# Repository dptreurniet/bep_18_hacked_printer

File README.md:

# bep_18_hacked_printer
Hacking a desktop inkjet printer to print micro-devices

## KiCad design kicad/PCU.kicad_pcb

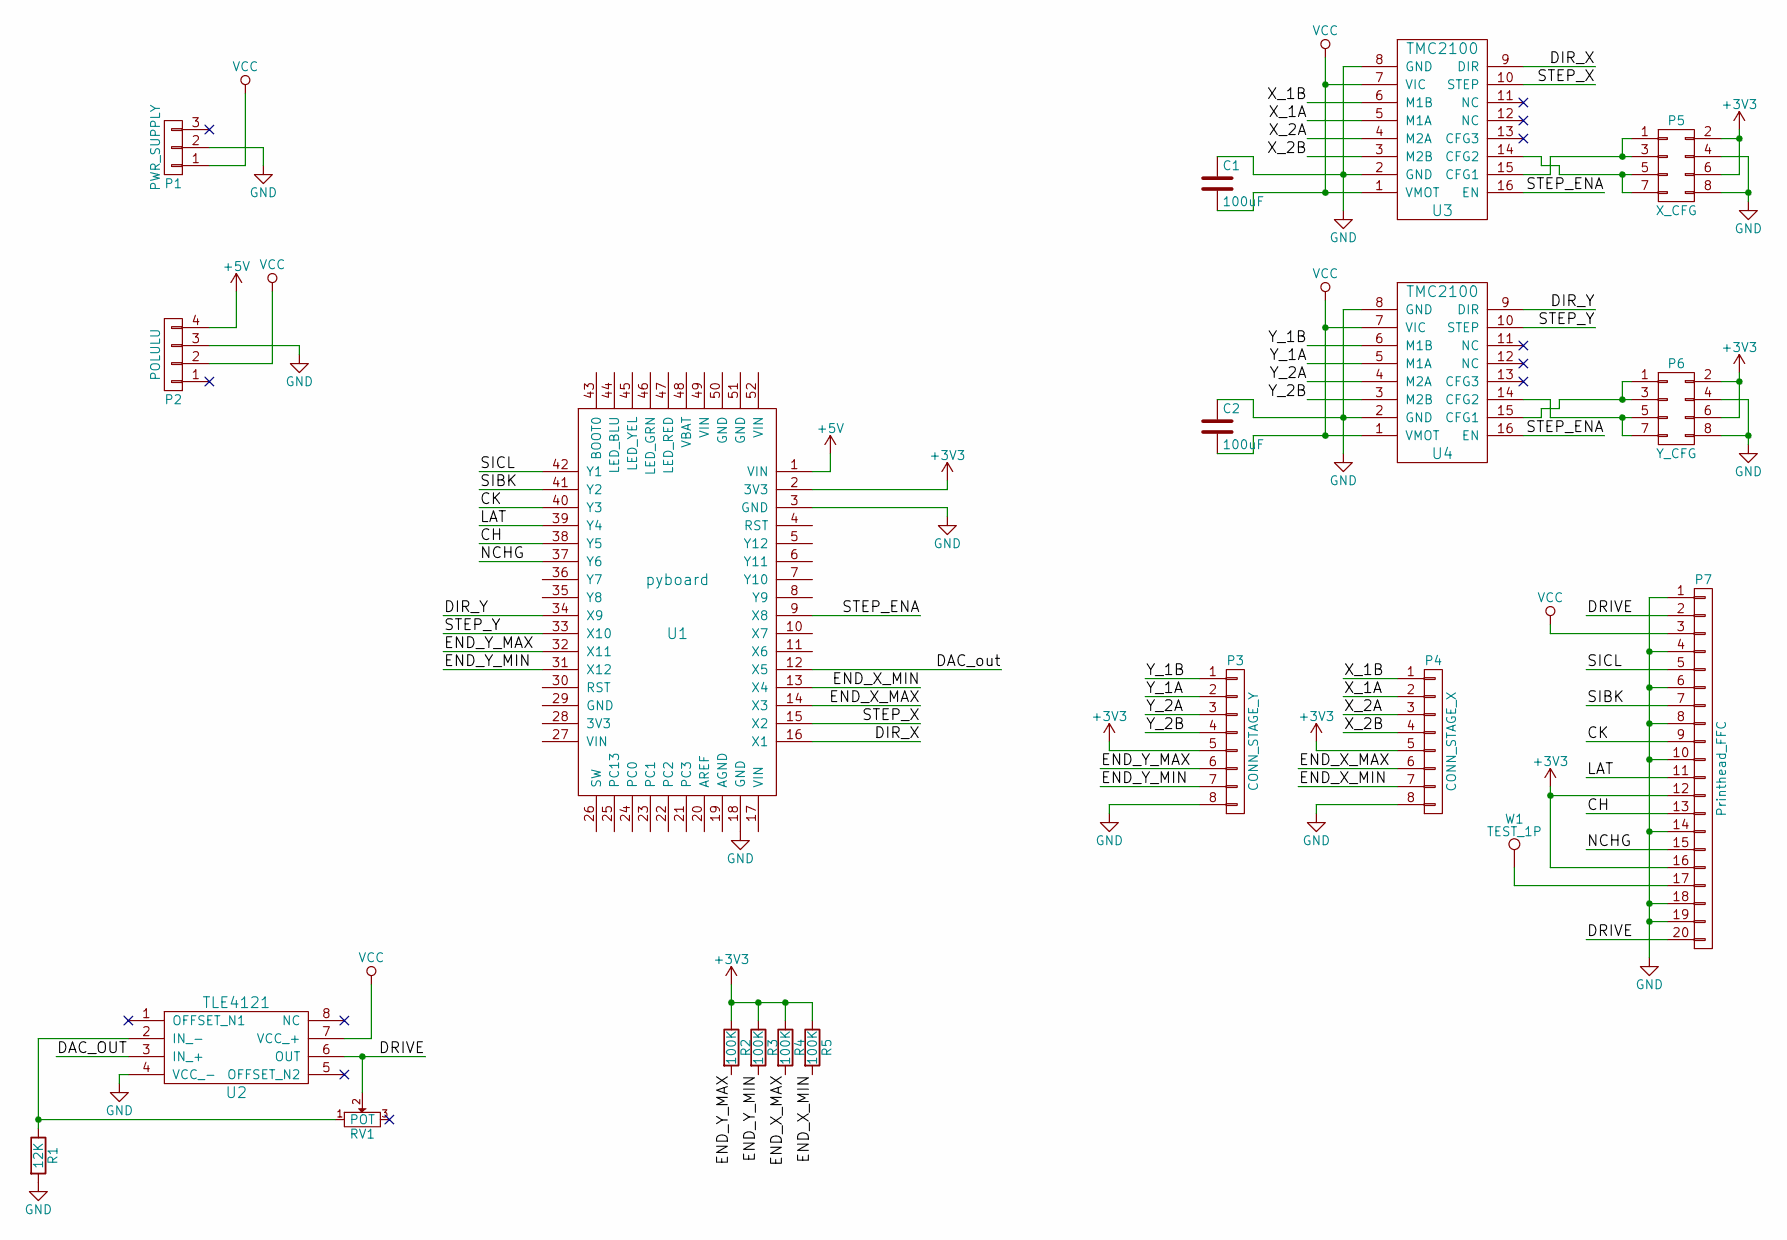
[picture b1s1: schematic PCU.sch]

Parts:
C1, C2: 100uF; Capacitor_D8_L11.5
P1: PWR_SUPPLY; Pin_Header_Straight_1x03
P2: POLULU; Polulu
P3: CONN_STAGE_Y; Pin_Header_Straight_1x08
P4: CONN_STAGE_X; Pin_Header_Straight_1x08
P5: X_CFG; Pin_Header_Straight_2x04
P6: Y_CFG; Pin_Header_Straight_2x04
P7: Printhead_FFC; 52030-2029
R1: 12K; Resistor_Horizontal_RM10mm
R2, R3, R4, R5: 100K; Resistor_Horizontal_RM10mm
RV1: POT; Potentiometer_Bourns_3339W_Angular_ScrewFront
U1: pyboard; Pyboard
U2: TLE4121; DIP-8_W7.62mm
U3, U4: TMC2100
W1: TEST_1P; SolderWirePad_single_1mmDrill

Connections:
+3V3: P3.5, P4.5, P5.2, P5.6, P6.2, P6.6, P7.12, P7.16, R2.1, R3.1, R4.1, R5.1, U1.2 (3V3)
+5V: P2.4, U1.1 (VIN)
/CH: P7.13, U1.38 (Y5)
/CK: P7.9, U1.40 (Y3)
/DAC_OUT: U1.12 (X5), U2.3 (IN_+)
/DIR_X: U1.16 (X1), U3.9 (DIR)
/DIR_Y: U1.34 (X9), U4.9 (DIR)
/DRIVE: P7.2, P7.20, RV1.2, U2.6 (OUT)
/END_X_MAX: P4.6, R4.2, U1.14 (X3)
/END_X_MIN: P4.7, R5.2, U1.13 (X4)
/END_Y_MAX: P3.6, R2.2, U1.32 (X11)
/END_Y_MIN: P3.7, R3.2, U1.31 (X12)
/LAT: P7.11, U1.39 (Y4)
/NCHG: P7.15, U1.37 (Y6)
/SIBK: P7.7, U1.41 (Y2)
/SICL: P7.5, U1.42 (Y1)
/STEP_ENA: U1.9 (X8), U3.16 (EN), U4.16 (EN)
/STEP_X: U1.15 (X2), U3.10 (STEP)
/STEP_Y: U1.33 (X10), U4.10 (STEP)
/X_1A: P4.2, U3.5 (M1A)
/X_1B: P4.1, U3.6 (M1B)
/X_2A: P4.3, U3.4 (M2A)
/X_2B: P4.4, U3.3 (M2B)
/Y_1A: P3.2, U4.5 (M1A)
/Y_1B: P3.1, U4.6 (M1B)
/Y_2A: P3.3, U4.4 (M2A)
/Y_2B: P3.4, U4.3 (M2B)
GND: C1.1, C2.1, P1.2, P2.3, P3.8, P4.8, P5.4, P5.8, P6.4, P6.8, P7.1, P7.4, P7.6, P7.8, P7.10, P7.14, P7.18, P7.19, R1.2, U1.3 (GND), U1.18 (GND), U2.4 (VCC_-), U3.2 (GND), U3.8 (GND), U4.2 (GND), U4.8 (GND)
unnamed: P5.1, P5.3, U3.15 (CFG1)
unnamed: P5.5, P5.7, U3.14 (CFG2)
unnamed: P6.1, P6.3, U4.15 (CFG1)
unnamed: P6.5, P6.7, U4.14 (CFG2)
unnamed: P7.17, W1.1
unnamed: R1.1, RV1.1, U2.2 (IN_-)
VCC: C1.2, C2.2, P1.1, P2.2, P7.3, U2.7 (VCC_+), U3.1 (VMOT), U3.7 (VIC), U4.1 (VMOT), U4.7 (VIC)

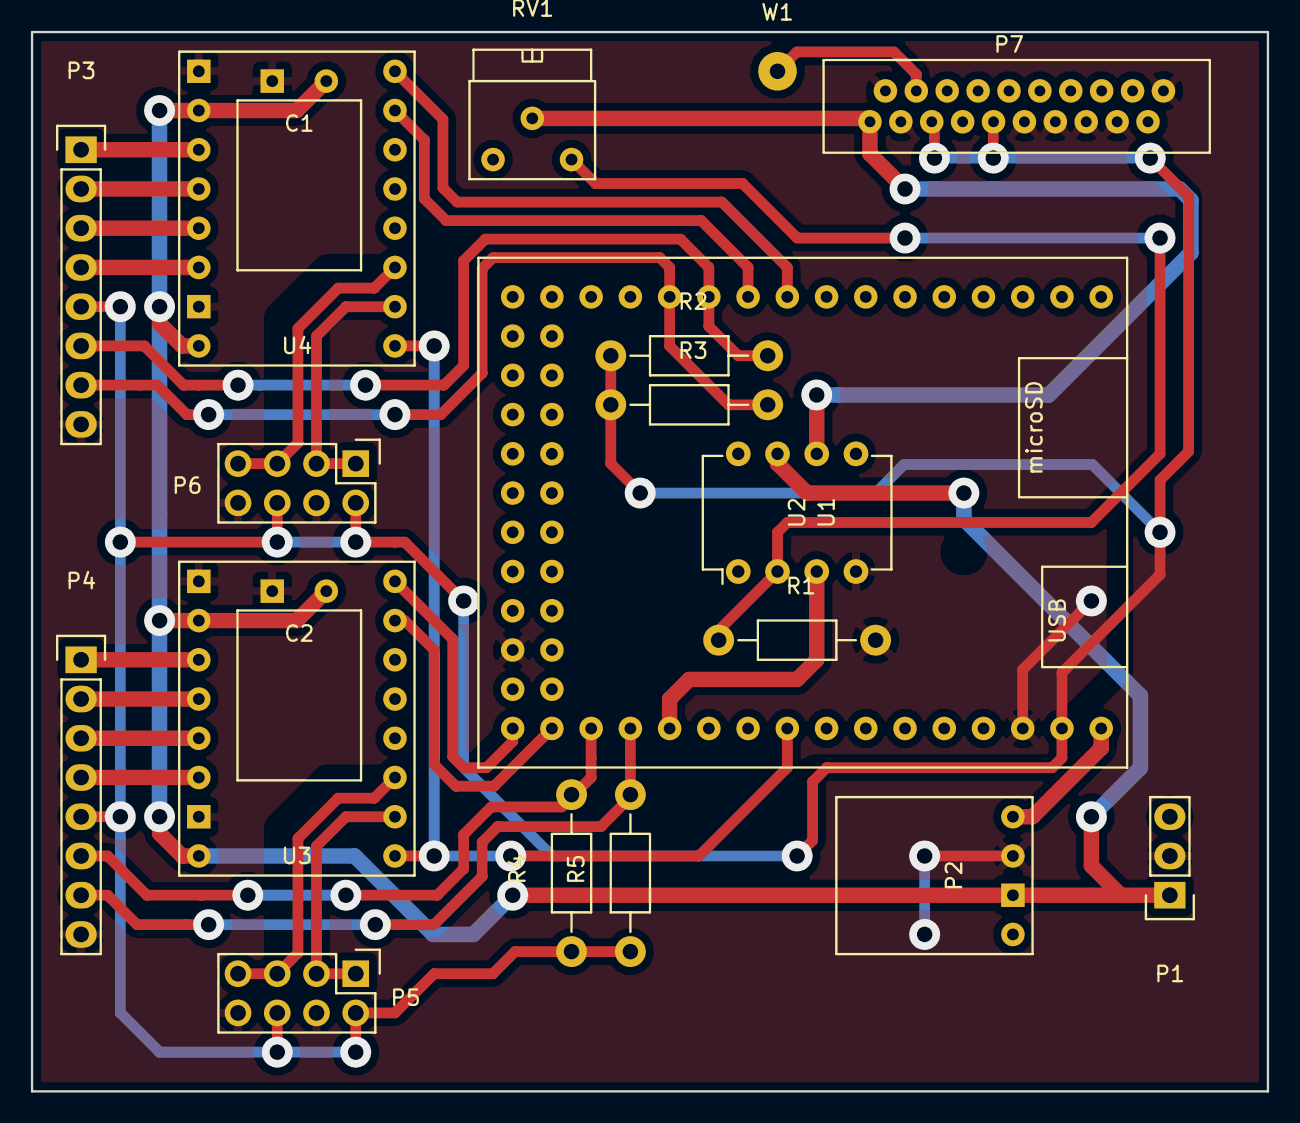
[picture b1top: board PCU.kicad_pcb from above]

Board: 2 copper layers, 80.0 x 68.6 mm, 20 parts (0 on the bottom side), 35 nets.

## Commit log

2018-04-04 Added sequence factory class
2018-04-04 Changed function name to PEP 8
2018-04-04 Added prototypes for controller classes
2018-04-04 Added gitignore
2018-04-04 Typo fix
2018-04-04 Fixed type
2018-04-04 Implemented move_to_position function
2018-04-04 Removed testing stuff
2018-04-04 Removed merge conflict stuff
2018-04-05 Started homing implementation and moved logging to stage class
2018-04-05 Moved to controllers folder
2018-04-05 Added ftdi gpio controller class
2018-04-06 Added version print
2018-04-06 Added motion stage controller
2018-04-06 Added printhead controller
2018-04-06 Added FTDI controller class
2018-04-06 Changed folders
2018-04-06 Added some leading and trailing zeroes for safety
2018-05-02 NEW START
2018-05-02 Added config file
2018-05-02 Config additions
2018-05-02 Added stage controller
